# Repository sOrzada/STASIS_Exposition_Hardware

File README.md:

# STASIS_Exposure_Hardware
This is the repository for the exposure hardware of the STASIS project.
The corresponding software can be found in this repository: https://github.com/sOrzada/STASIS_Control

by Stephan Orzada @ German Cancer Research Center (DKFZ) 

# Overview
The STASIS RF exposure system is an open-source hardware and software platform designed for implant testing under exposure to radiofrequency (RF) fields, such as those encountered in the environment of an MRI system. For this purpose, the target RF frequency is 128 MHz, corresponding to the resonant frequency of protons in a 3 Tesla magnetic field. The system is capable of transmitting on eight independent RF channels, enabling parallel transmission.
To ensure the design is easily accessible to potential users, all design files and software are publicly available and can be accessed via the following repositories:
https://github.com/sOrzada/STASIS_Exposure_Hardware
https://github.com/sOrzada/STASIS_Control
All hardware components of the exposure system are licensed under the CERN-OHL-W while the software is licensed under a GNU GPL v3. In addition the project has been submitted to the conformity assessment body of the Open Source Imaging Initiative e.V. (https://www.opensourceimaging.org) to assess its open source status according to DIN SPEC 3105.  
To further improve accessibility, standard components with long production lifespans were selected wherever possible. For example, standard logic components were used instead of specialised microcontrollers or FPGAs.

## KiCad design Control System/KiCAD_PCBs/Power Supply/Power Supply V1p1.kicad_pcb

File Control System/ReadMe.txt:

This Folder contains the PCBs and Housings for the Control System of the STASIS project's RF exposition system.
The PCBs are provided in two different formats: Eagle and KiCAD.
The Housings-folder contains .step files for the housings and front panels of the Eurocards.

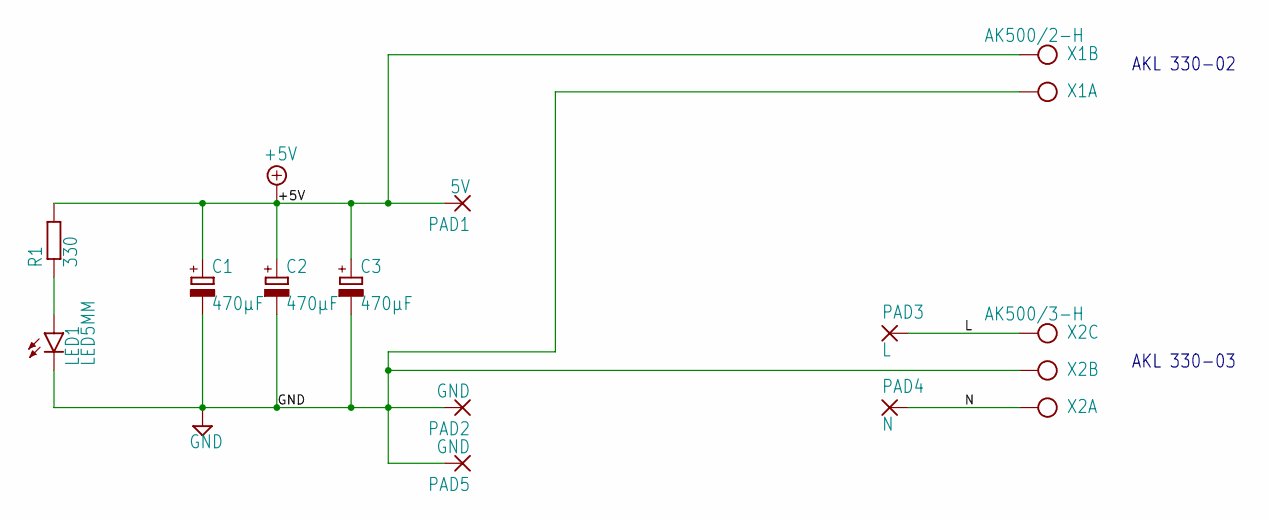
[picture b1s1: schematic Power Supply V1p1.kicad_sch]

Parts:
C1, C2, C3: 470µF; E5-10,5
LED1: LED5MM
PAD1: 5V; SMD2,54-5,08
PAD2, PAD5: GND; SMD2,54-5,08
PAD3: L; SMD2,54-5,08
PAD4: N; SMD2,54-5,08
R1: 330; R1206
X1: AK500/2-H; AK500_2-H
X2: AK500/3-H; AK500_3-H

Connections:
+5V: C1.+, C2.+, C3.+, PAD1.1, R1.2, X1.2
GND: C1.-, C2.-, C3.-, LED1.K (C), PAD2.1, PAD5.1, X1.1, X2.2
L: PAD3.1, X2.3
N: PAD4.1, X2.1
unnamed: LED1.A, R1.1

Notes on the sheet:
AKL 330-02
AKL 330-03

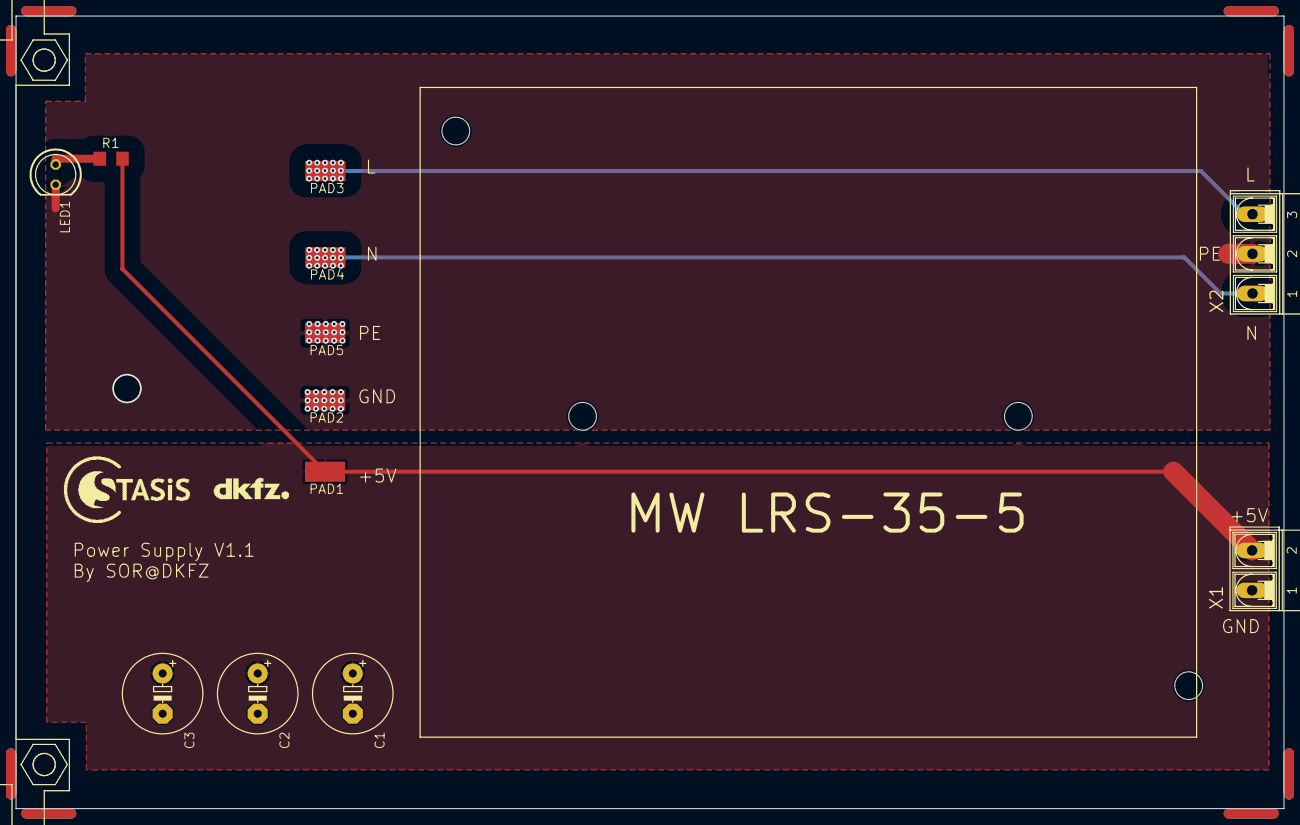
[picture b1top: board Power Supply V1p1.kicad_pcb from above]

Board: 2 copper layers, 160.0 x 100.0 mm, 19 parts (0 on the bottom side), 5 nets.

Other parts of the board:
@HOLE0, @HOLE1, @HOLE2, @HOLE3: (no value)
U$1: EK-FP_79
U$2: LOGO_STASIS
U$3: LOGO_DKFZ

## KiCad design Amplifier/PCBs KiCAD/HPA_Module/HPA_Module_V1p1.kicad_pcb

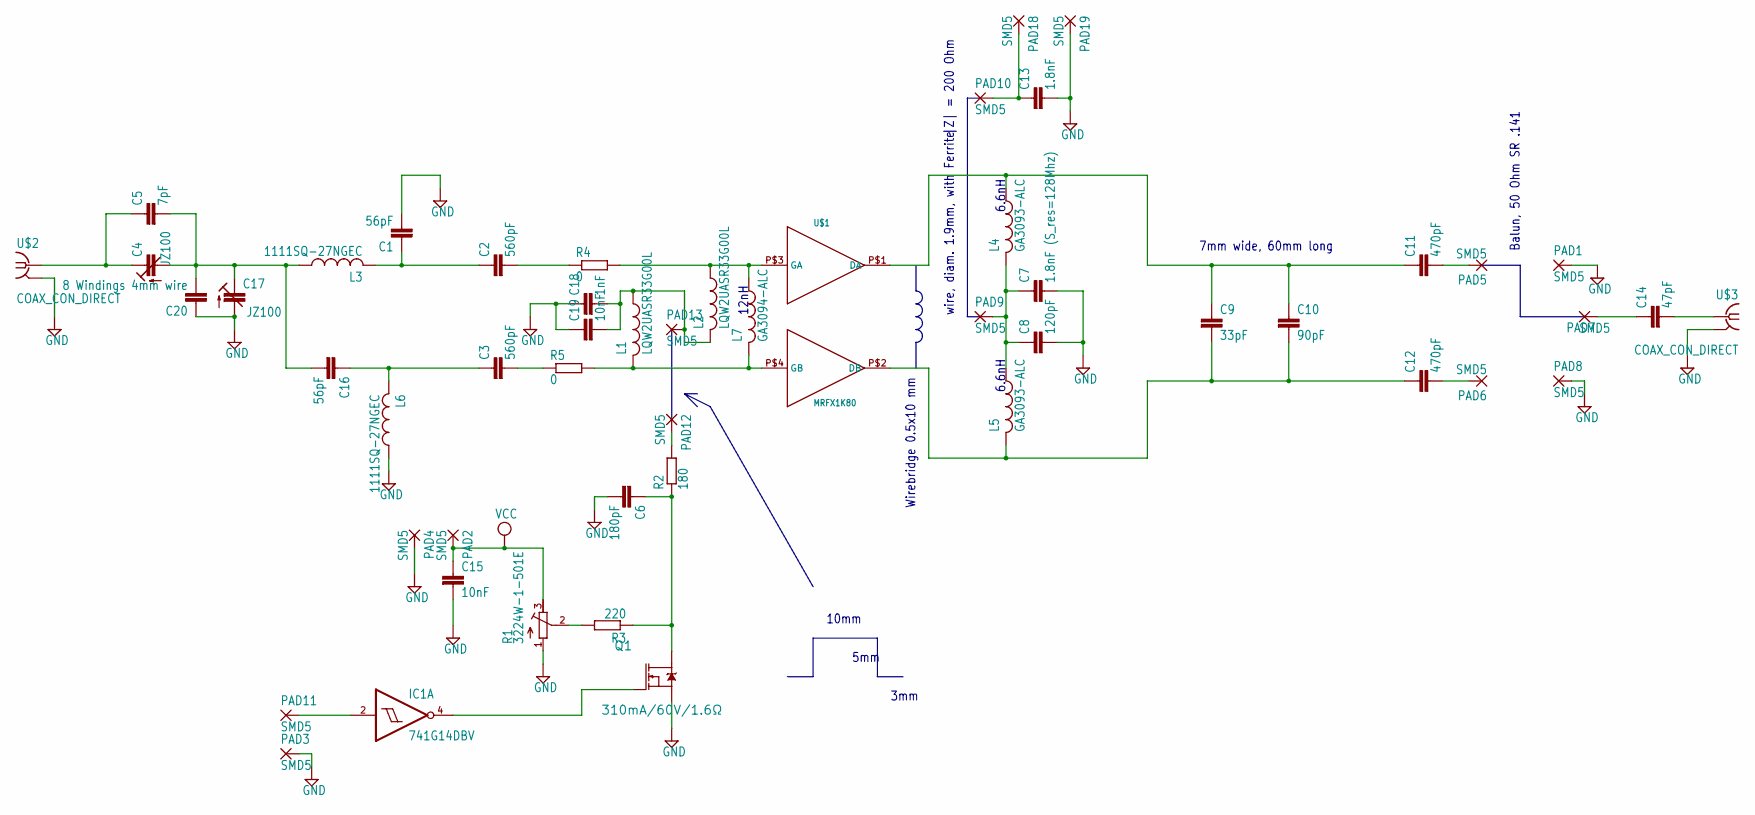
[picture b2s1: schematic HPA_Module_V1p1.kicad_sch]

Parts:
C1, C16: 56pF; C1210
C2, C3: 560pF; C1210
C4, C17: JZ100; CTRIM3018_12
C5: 7pF; C1210K
C6: 180pF; C0805
C7: 1.8nF (S_res=128Mhz); C1210
C8: 120pF; C1210
C9: 33pF; C2220K
C10: 90pF; C2220K
C11, C12: 470pF; C1210
C13: 1.8nF; C1210
C14: 47pF; C1210
C15, C19: 10nF; C0805
C18: 1nF; C0805
C20: 8 Windings 4mm wire; C1210K
IC1: 741G14DBV; SOT23-5
L1, L2: LQW2UASR33G00L; L2825P
L3, L6: 1111SQ-27NGEC; L2825P
L4, L5: GA3093-ALC; L4532P
L7: GA3094-ALC; L4532P
PAD1, PAD2, PAD3, PAD4, PAD5, PAD6, PAD7, PAD8, PAD9, PAD10, PAD11, PAD12, PAD13, PAD18, PAD19: SMD5; SMD2,54-5,08
Q1: 310mA/60V/1.6Ω; SOT323
R1: 3224W-1-501E; RTRIM3224W
R2: 180; R0805
R3: 220; R0805
R4, R5: 0; R1206
U$1: MRFX1K80; NI-1230H-4S
U$2, U$3: COAX_CON_DIRECT; COAX.141

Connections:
GND: C1.2, C6.2, C7.2, C8.2, C13.2, C15.2, C17.- (A), C18.1, C19.1, C20.1, IC1.3 (GND), L6.1, PAD1.1, PAD3.1, PAD4.1, PAD8.1, PAD19.1, Q1.2 (S), R1.1 (A), U$2.P$2 (GND@1), U$3.P$2 (GND@1)
unnamed: L1.2, L7.2, R5.2, U$1.P$4 (GB)
unnamed: L2.1, L7.1, R4.2, U$1.P$3 (GA)
unnamed: C18.2, C19.2, L1.1, L2.2, PAD13.1
unnamed: C9.1, C10.1, C11.1, L4.1, U$1.P$1 (DA)
unnamed: C1.1, C2.1, L3.2
unnamed: C3.1, C16.1, L6.2
unnamed: C4.- (A), C5.2, C16.2, C17.+ (E), C20.2, L3.1
unnamed: C9.2, C10.2, C12.1, L5.2, U$1.P$2 (DB)
unnamed: C4.+ (E), C5.1, U$2.P$1 (1)
unnamed: C7.1, C8.1, L4.2, L5.1, PAD9.1
unnamed: C6.1, Q1.3 (D), R2.1, R3.1
unnamed: C11.2, PAD5.1
unnamed: C12.2, PAD6.1
unnamed: C13.1, PAD10.1, PAD18.1
unnamed: R1.2 (S), R3.2
unnamed: C14.1, PAD7.1
unnamed: C14.2, U$3.P$1 (1)
unnamed: IC1.4 (O), Q1.1 (G)
unnamed: PAD12.1, R2.2
unnamed: IC1.2 (I), PAD11.1
unnamed: C2.2, R4.1
unnamed: C3.2, R5.1
VCC: C15.1, IC1.5 (VCC), PAD2.1, R1.3 (E)

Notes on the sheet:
Wirebridge 0.5x10 mm
10mm
6.6nH
7mm wide, 60mm long
5mm
3mm
wire, diam. 1.9mm, with Ferrite
Balun, 50 Ohm SR .141
|Z| = 200 Ohm
12nH

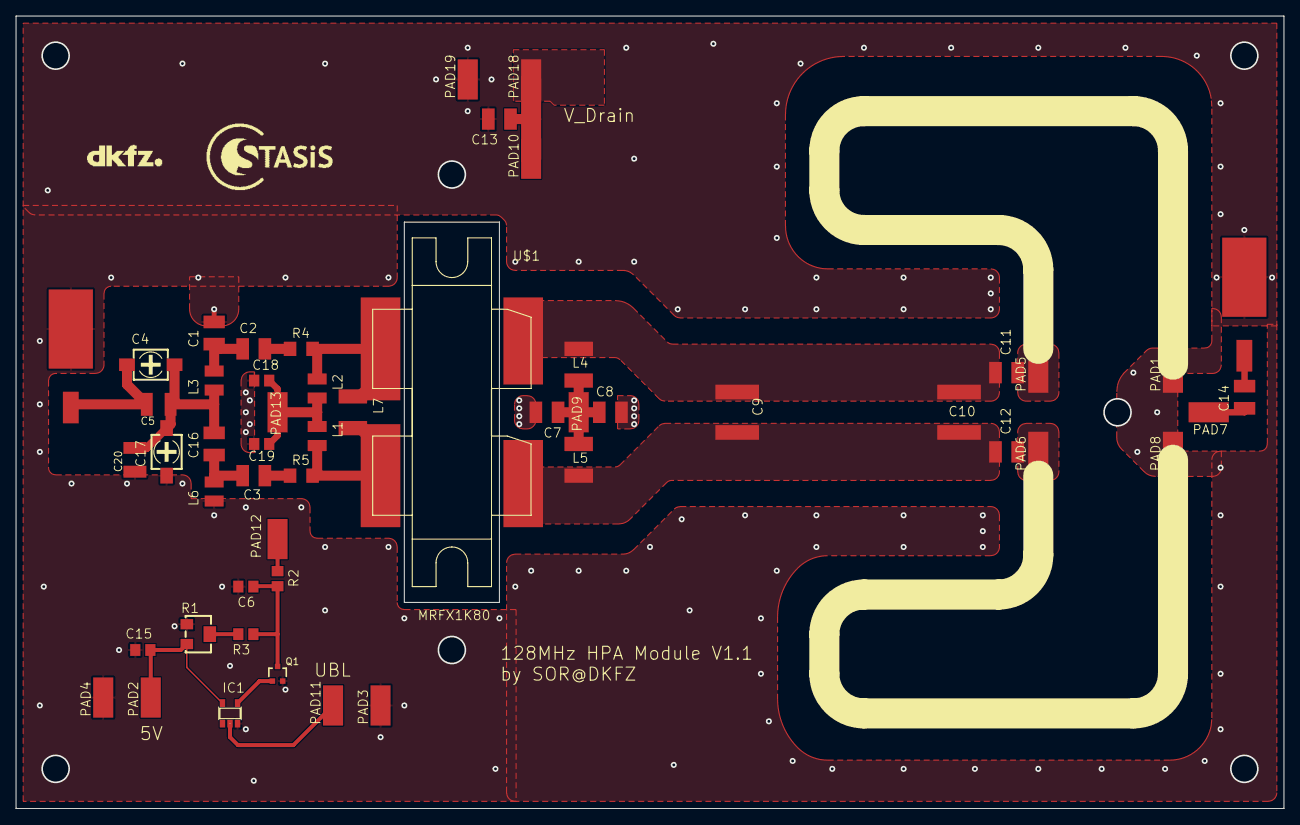
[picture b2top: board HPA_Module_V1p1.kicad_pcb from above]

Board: 2 copper layers, 160.0 x 100.0 mm, 54 parts (0 on the bottom side), 24 nets.

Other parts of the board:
U$4: LOGO_DKFZ
U$5: LOGO_STASIS

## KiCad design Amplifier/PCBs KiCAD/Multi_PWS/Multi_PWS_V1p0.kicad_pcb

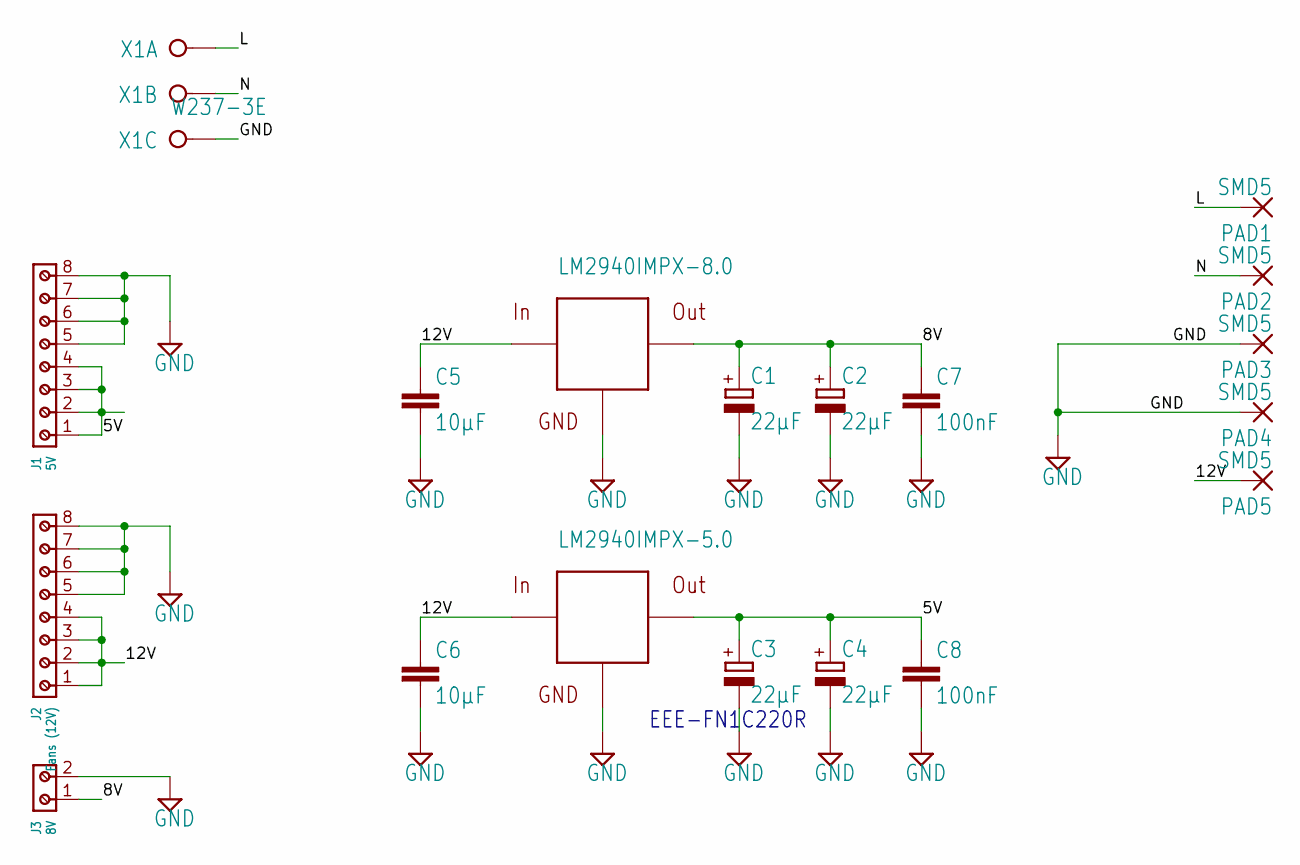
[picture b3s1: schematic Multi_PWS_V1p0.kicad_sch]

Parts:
C1, C2, C3, C4: 22µF; PANASONIC_B
C5, C6: 10µF; C1210
C7, C8: 100nF; C1210
J1: 5V; 691210910008
J2: Fans (12V); 691210910008
J3: 8V; 691210910002
PAD1, PAD2, PAD3, PAD4, PAD5: SMD5; SMD2,54-5,08
U$1: LM2940IMPX-8.0; SOT223
U$2: LM2940IMPX-5.0; SOT223
X1: W237-3E

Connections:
5V: C3.+, C4.+, C8.1, J1.1, J1.2, J1.3, J1.4, U$2.3 (VCC)
8V: C1.+, C2.+, C7.1, J3.1, U$1.3 (VCC)
12V: C5.1, C6.1, J2.1, J2.2, J2.3, J2.4, PAD5.1, U$1.1 (IN), U$2.1 (IN)
GND: C1.-, C2.-, C3.-, C4.-, C5.2, C6.2, C7.2, C8.2, J1.5, J1.6, J1.7, J1.8, J2.5, J2.6, J2.7, J2.8, J3.2, PAD3.1, PAD4.1, U$1.2 (GND), U$1.4 (GND), U$2.2 (GND), U$2.4 (GND), X1.3
L: PAD1.1, X1.1
N: PAD2.1, X1.2

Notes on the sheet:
EEE-FN1C220R

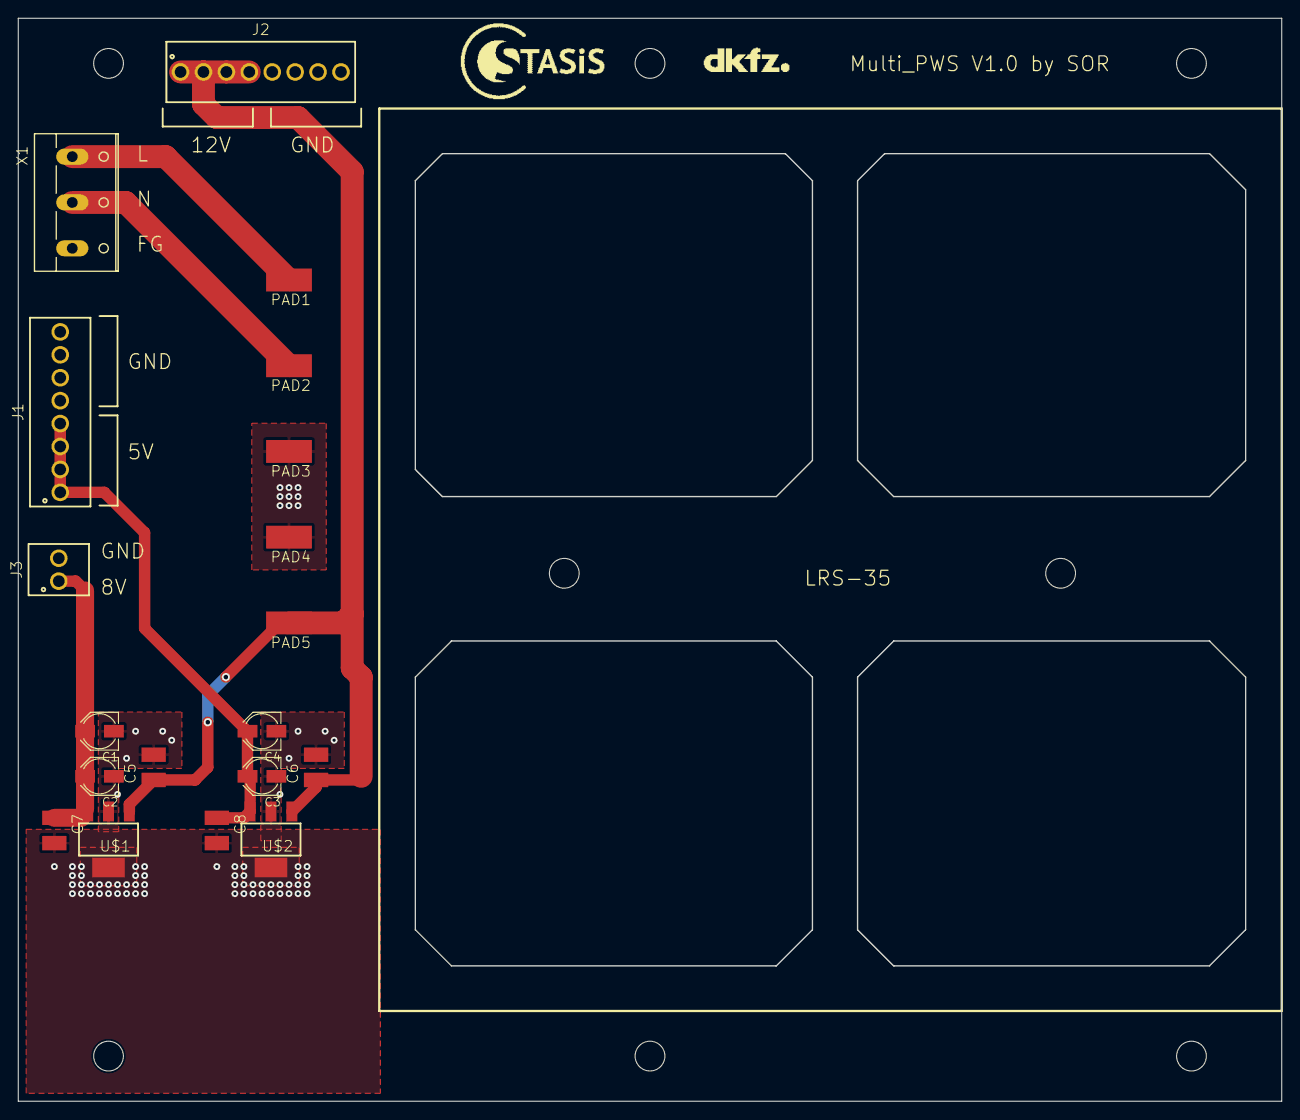
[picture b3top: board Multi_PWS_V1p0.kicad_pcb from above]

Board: 2 copper layers, 140.0 x 120.0 mm, 29 parts (0 on the bottom side), 6 nets.

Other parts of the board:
@HOLE0, @HOLE1, @HOLE2, @HOLE3, @HOLE4, @HOLE5, @HOLE6, @HOLE7: (no value)
U$3: LOGO_DKFZ
U$4: LOGO_STASIS

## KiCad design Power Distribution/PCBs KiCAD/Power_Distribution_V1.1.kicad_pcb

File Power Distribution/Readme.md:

# Power Distribution
This folder contains the data for the power distribution of the STASIS RF exposition system.
The Power Distribution is provides a simple switch (and emergency switch) to switch the system's power on and off.
Furthermore, it switches each amplifier on 3s after the previous amplifier to prevent circuit breakers from acting.

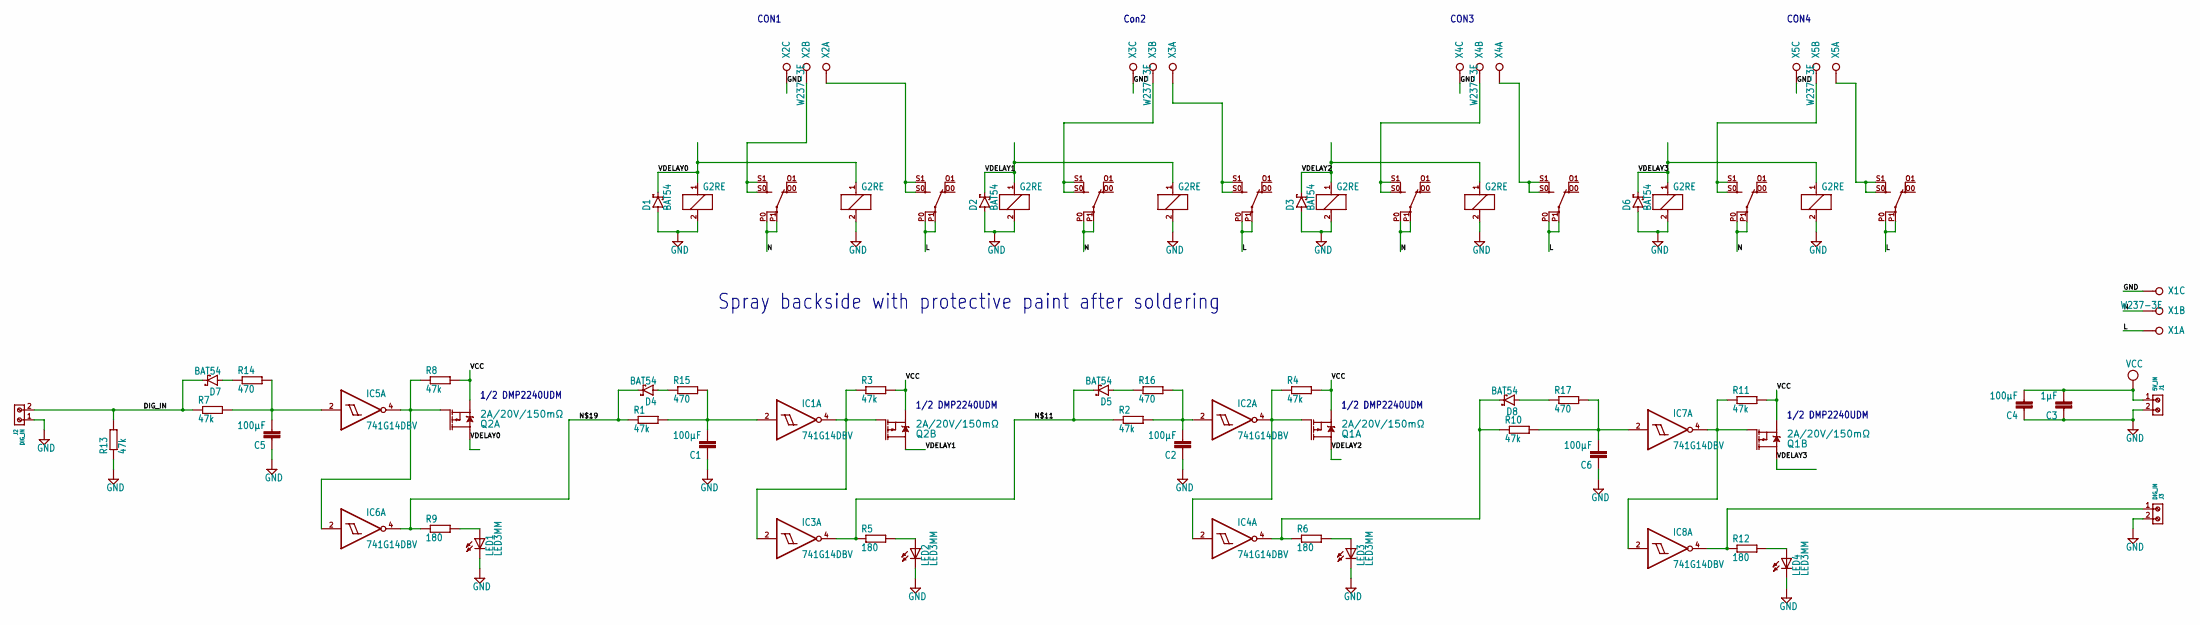
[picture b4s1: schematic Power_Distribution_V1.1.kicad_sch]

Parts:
C1, C2, C4, C5, C6: 100µF; C1210
C3: 1µF; C1210
D1, D2, D3, D4, D5, D6, D7, D8: BAT54; SOT23
IC1, IC2, IC3, IC4, IC5, IC6, IC7, IC8: 741G14DBV; SOT23-5
J1: 5V_IN; 691210910002
J2, J3: DIG_IN; 691210910002
K1, K2, K3, K4, K5, K6, K7, K8: G2RE
LED1, LED2, LED3, LED4: LED3MM
Q1, Q2: 2A/20V/150mΩ; SOT26
R1, R2, R3, R4, R7, R8, R10, R11, R13: 47k; R0805
R5, R6, R9, R12: 180; R0805
R14, R15, R16, R17: 470; R0805
X1, X2, X3, X4, X5: W237-3E

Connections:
DIG_IN: D7.3 (C), J2.2, R7.1, R13.2
GND: C1.1, C2.1, C3.1, C4.1, C5.1, C6.1, D1.1 (A), D2.1 (A), D3.1 (A), D6.1 (A), IC1.3 (GND), IC2.3 (GND), IC3.3 (GND), IC4.3 (GND), IC5.3 (GND), IC6.3 (GND), IC7.3 (GND), IC8.3 (GND), J1.2, J2.1, J3.2, K1.2, K2.2, K3.2, K4.2, K5.2, K6.2, K7.2, K8.2, LED1.K (C), LED2.K (C), LED3.K (C), LED4.K (C), R13.1, X1.3, X2.3, X3.3, X4.3, X5.3
L: K2.P0 (P@1), K2.P1, K4.P0 (P@1), K4.P1, K6.P0 (P@1), K6.P1, K8.P0 (P@1), K8.P1, X1.1
N: K1.P0 (P@1), K1.P1, K3.P0 (P@1), K3.P1, K5.P0 (P@1), K5.P1, K7.P0 (P@1), K7.P1, X1.2
unnamed: K1.S0 (S), K1.S1 (S@1), X2.2
unnamed: K2.S0 (S), K2.S1 (S@1), X2.1
unnamed: K3.S0 (S), K3.S1 (S@1), X3.2
unnamed: K4.S0 (S), K4.S1 (S@1), X3.1
unnamed: K5.S0 (S), K5.S1 (S@1), X4.2
unnamed: K6.S0 (S), K6.S1 (S@1), X4.1
unnamed: IC1.4 (O), IC3.2 (I), Q2.G2 (G), R3.1
unnamed: IC2.4 (O), IC4.2 (I), Q1.G1 (G), R4.1
unnamed: C2.2, IC2.2 (I), R2.2, R16.2
unnamed: C1.2, IC1.2 (I), R1.2, R15.2
unnamed: D5.3 (C), IC3.4 (O), R2.1, R5.1
unnamed: LED2.A, R5.2
unnamed: D8.3 (C), IC4.4 (O), R6.1, R10.1
unnamed: LED3.A, R6.2
unnamed: K7.S0 (S), K7.S1 (S@1), X5.2
unnamed: K8.S0 (S), K8.S1 (S@1), X5.1
unnamed: IC5.4 (O), IC6.2 (I), Q2.G1 (G), R8.1
unnamed: C5.2, IC5.2 (I), R7.2, R14.2
unnamed: D4.3 (C), IC6.4 (O), R1.1, R9.1
unnamed: LED1.A, R9.2
unnamed: IC7.4 (O), IC8.2 (I), Q1.G2 (G), R11.1
unnamed: C6.2, IC7.2 (I), R10.2, R17.2
unnamed: IC8.4 (O), J3.1, R12.1
unnamed: LED4.A, R12.2
unnamed: D7.1 (A), R14.1
unnamed: D4.1 (A), R15.1
unnamed: D5.1 (A), R16.1
unnamed: D8.1 (A), R17.1
VCC: C3.2, C4.2, IC1.5 (VCC), IC2.5 (VCC), IC3.5 (VCC), IC4.5 (VCC), IC5.5 (VCC), IC6.5 (VCC), IC7.5 (VCC), IC8.5 (VCC), J1.1, Q1.S1 (S), Q1.S2 (S), Q2.S1 (S), Q2.S2 (S), R3.2, R4.2, R8.2, R11.2
VDELAY0: D1.3 (C), K1.1, K2.1, Q2.D1 (D)
VDELAY1: D2.3 (C), K3.1, K4.1, Q2.D2 (D)
VDELAY2: D3.3 (C), K5.1, K6.1, Q1.D1 (D)
VDELAY3: D6.3 (C), K7.1, K8.1, Q1.D2 (D)

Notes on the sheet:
Spray backside with protective paint after soldering~{}
1/2 DMP2240UDM
CON3
CON4
Con2
CON1

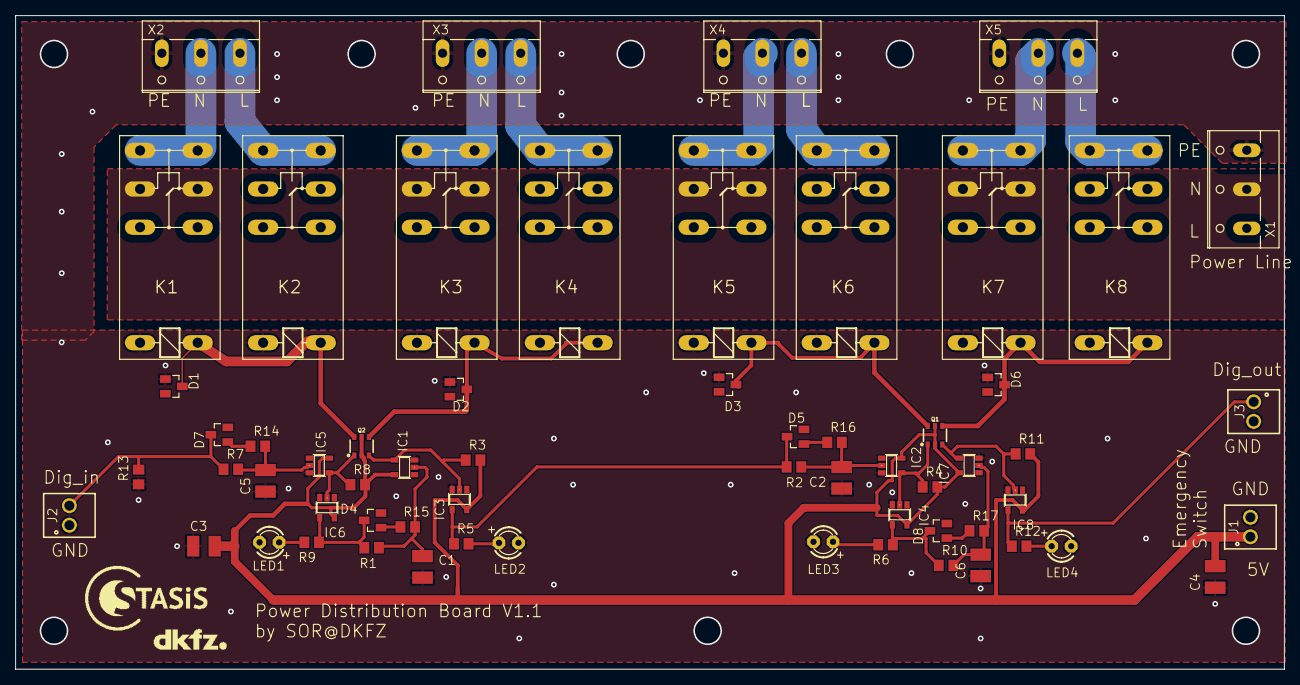
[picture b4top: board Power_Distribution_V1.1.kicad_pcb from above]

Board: 2 copper layers, 165.0 x 85.0 mm, 63 parts (0 on the bottom side), 37 nets.

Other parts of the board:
U$1: LOGO_STASIS
U$2: LOGO_DKFZ

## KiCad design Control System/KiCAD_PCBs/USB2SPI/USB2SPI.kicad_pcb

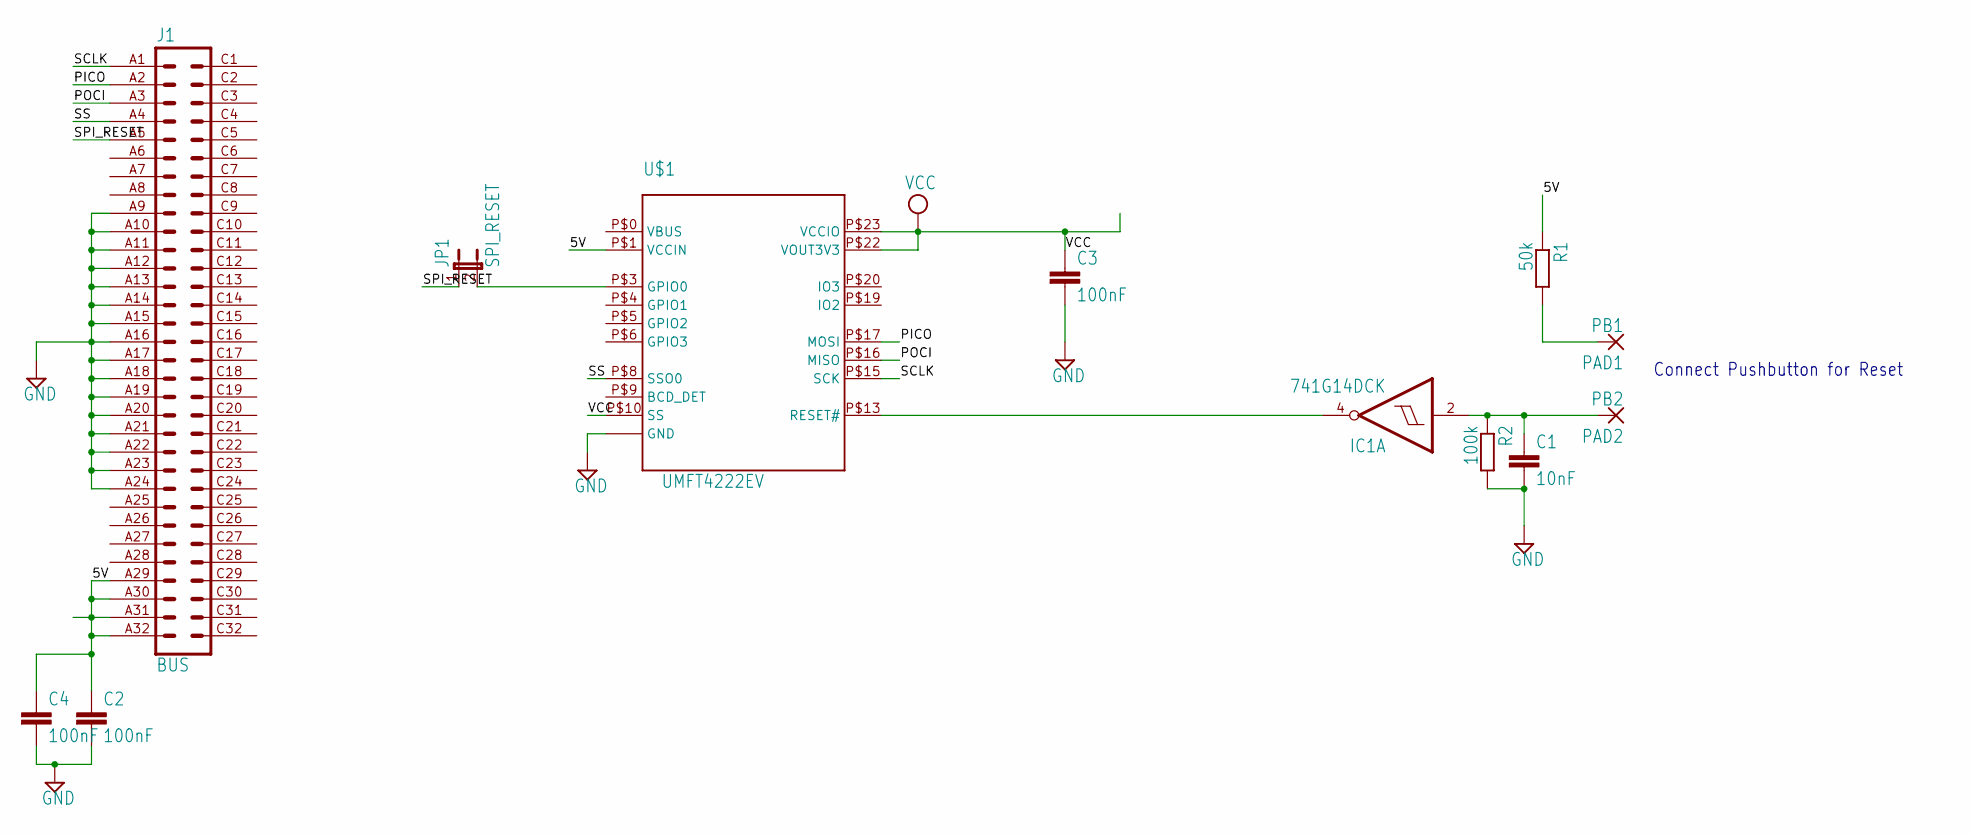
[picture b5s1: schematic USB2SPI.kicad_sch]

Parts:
C1: 10nF; C0603
C2, C3, C4: 100nF; C0603
IC1: 741G14DCK; SC70-5
J1: BUS; VG64P
JP1: SPI_RESET; JP1
PAD1: PB1; SMD2,54-5,08
PAD2: PB2; SMD2,54-5,08
R1: 50k; R0603
R2: 100k; R0603
U$1: UMFT4222EV

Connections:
5V: C2.1, C4.1, J1.A29, J1.A30, J1.A31, J1.A32, R1.1, U$1.P$1 (VCCIN)
GND: C1.2, C2.2, C3.2, C4.2, IC1.3 (GND), J1.A9, J1.A10, J1.A11, J1.A12, J1.A13, J1.A14, J1.A15, J1.A16, J1.A17, J1.A18, J1.A19, J1.A20, J1.A21, J1.A22, J1.A23, J1.A24, R2.2, U$1.P$2 (GND), U$1.P$7 (GND), U$1.P$11 (GND), U$1.P$12 (GND), U$1.P$14 (GND), U$1.P$18 (GND), U$1.P$21 (GND)
unnamed: JP1.2, U$1.P$3 (GPIO0)
unnamed: IC1.4 (O), U$1.P$13 (RESET#)
unnamed: C1.1, IC1.2 (I), PAD2.1, R2.1
unnamed: PAD1.1, R1.2
PICO: J1.A2, U$1.P$17 (MOSI)
POCI: J1.A3, U$1.P$16 (MISO)
SCLK: J1.A1, U$1.P$15 (SCK)
SPI_RESET: J1.A5, JP1.1
SS: J1.A4, U$1.P$8 (SSO0)
VCC: C3.1, IC1.5 (VCC), U$1.P$10 (SS), U$1.P$22 (VOUT3V3), U$1.P$23 (VCCIO)

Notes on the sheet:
Connect Pushbutton for Reset

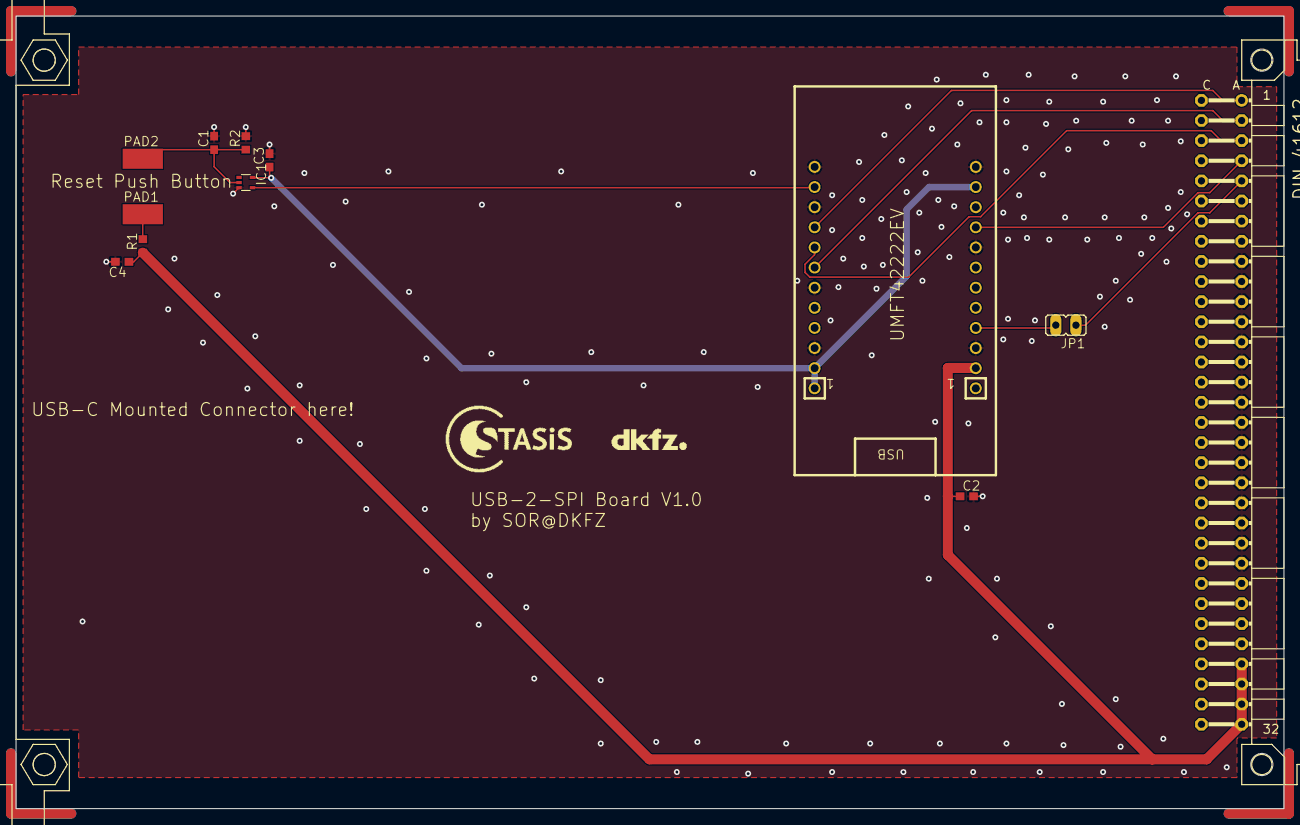
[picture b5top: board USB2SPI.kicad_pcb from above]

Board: 2 copper layers, 160.0 x 100.0 mm, 14 parts (0 on the bottom side), 12 nets.

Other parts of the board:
U$2: LOGO_STASIS
U$3: LOGO_DKFZ

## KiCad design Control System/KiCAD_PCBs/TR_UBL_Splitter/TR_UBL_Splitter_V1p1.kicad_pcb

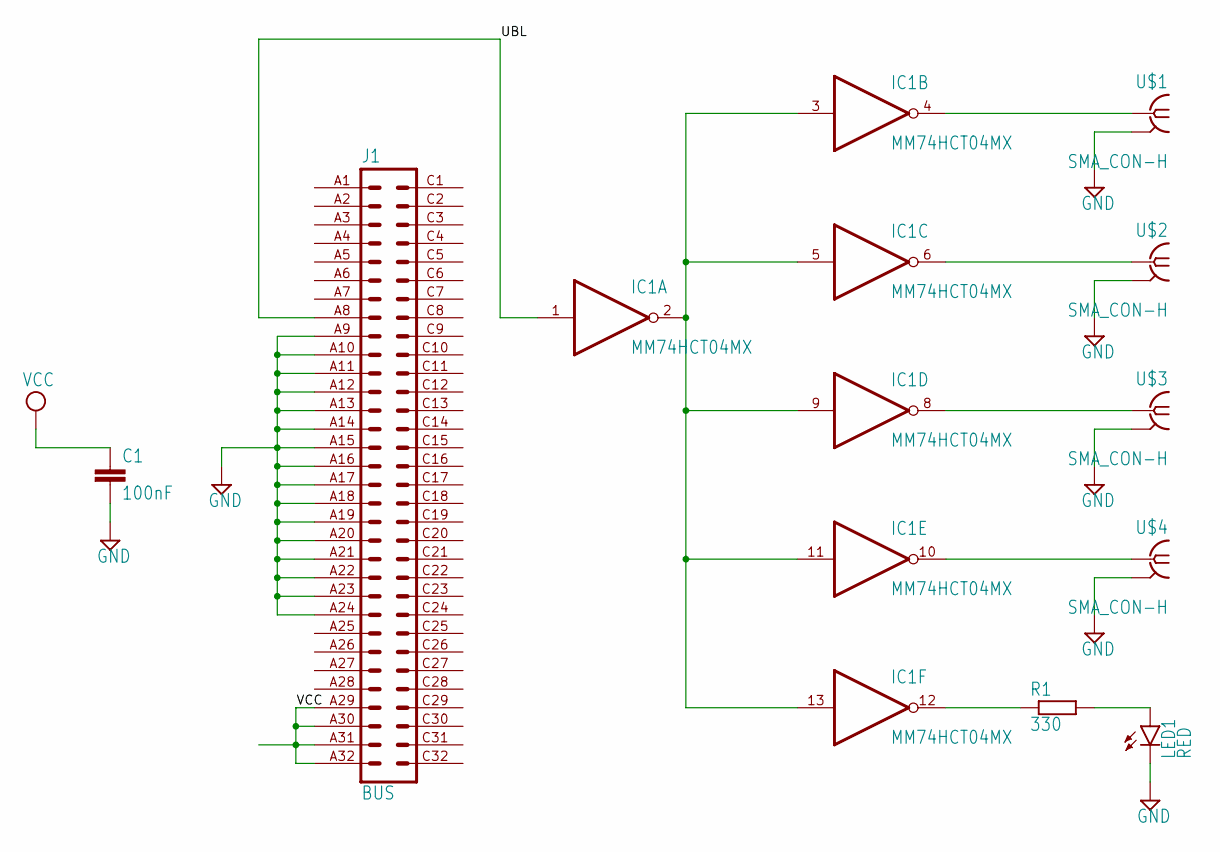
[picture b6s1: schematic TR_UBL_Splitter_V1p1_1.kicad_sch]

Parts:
C1: 100nF; C0603
IC1: MM74HCT04MX; SO14
J1: BUS; VG64P
LED1: RED; LED3MM
R1: 330; R0603
U$1, U$2, U$3, U$4: SMA_CON-H; BU-SMA-H

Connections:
GND: C1.2, IC1.7 (GND), J1.A9, J1.A10, J1.A11, J1.A12, J1.A13, J1.A14, J1.A15, J1.A16, J1.A17, J1.A18, J1.A19, J1.A20, J1.A21, J1.A22, J1.A23, J1.A24, LED1.K (C), U$1.2 (GND@1), U$1.3 (GND@1), U$1.4 (GND@1), U$1.5 (GND@1), U$2.2 (GND@1), U$2.3 (GND@1), U$2.4 (GND@1), U$2.5 (GND@1), U$3.2 (GND@1), U$3.3 (GND@1), U$3.4 (GND@1), U$3.5 (GND@1), U$4.2 (GND@1), U$4.3 (GND@1), U$4.4 (GND@1), U$4.5 (GND@1)
unnamed: IC1.2 (O), IC1.3 (I), IC1.5 (I), IC1.9 (I), IC1.11 (I), IC1.13 (I)
unnamed: IC1.4 (O), U$1.1
unnamed: LED1.A, R1.2
unnamed: IC1.6 (O), U$2.1
unnamed: IC1.12 (O), R1.1
unnamed: IC1.8 (O), U$3.1
unnamed: IC1.10 (O), U$4.1
UBL: IC1.1 (I), J1.A8
VCC: C1.1, IC1.14 (VCC), J1.A29, J1.A30, J1.A31, J1.A32

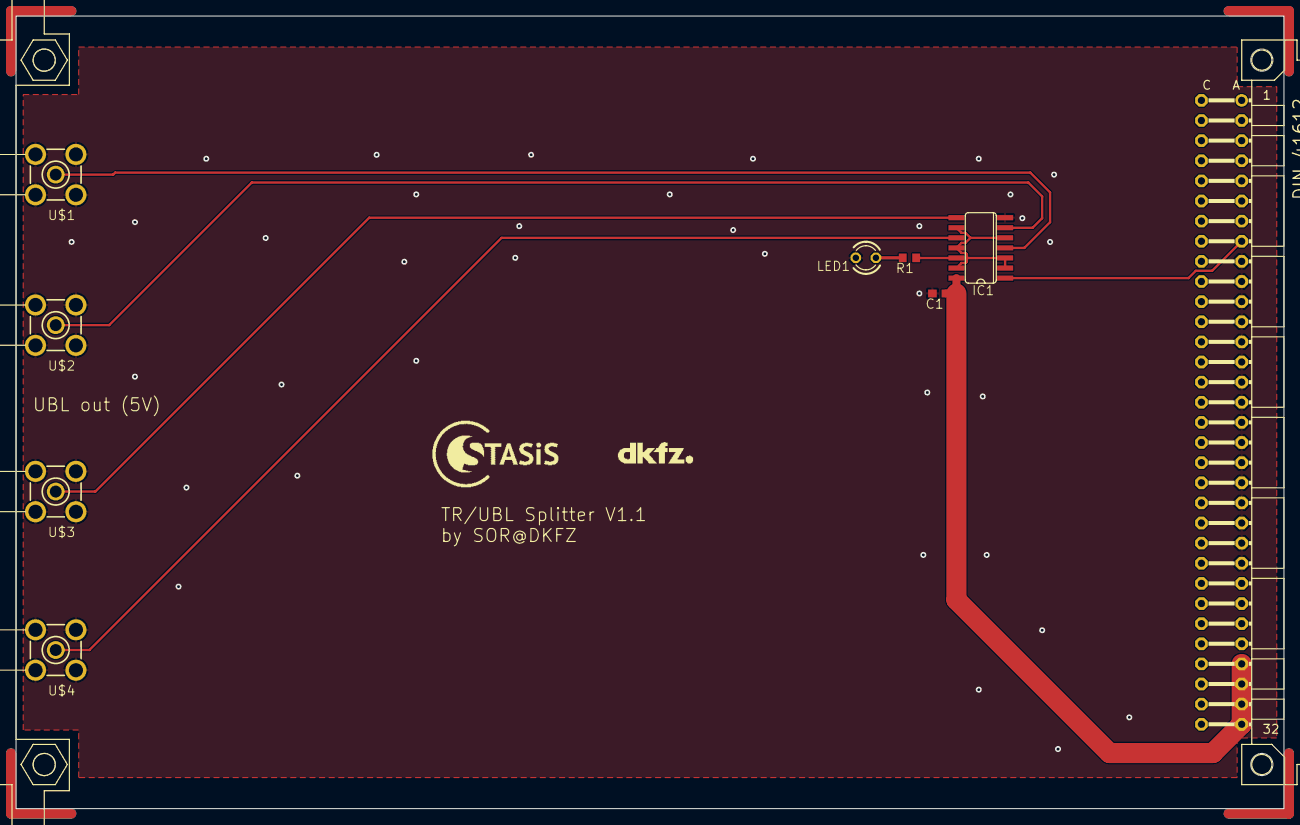
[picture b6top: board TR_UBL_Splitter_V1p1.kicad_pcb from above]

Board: 2 copper layers, 160.0 x 100.0 mm, 11 parts (0 on the bottom side), 10 nets.

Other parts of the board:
U$5: LOGO_STASIS
U$6: LOGO_DKFZ
